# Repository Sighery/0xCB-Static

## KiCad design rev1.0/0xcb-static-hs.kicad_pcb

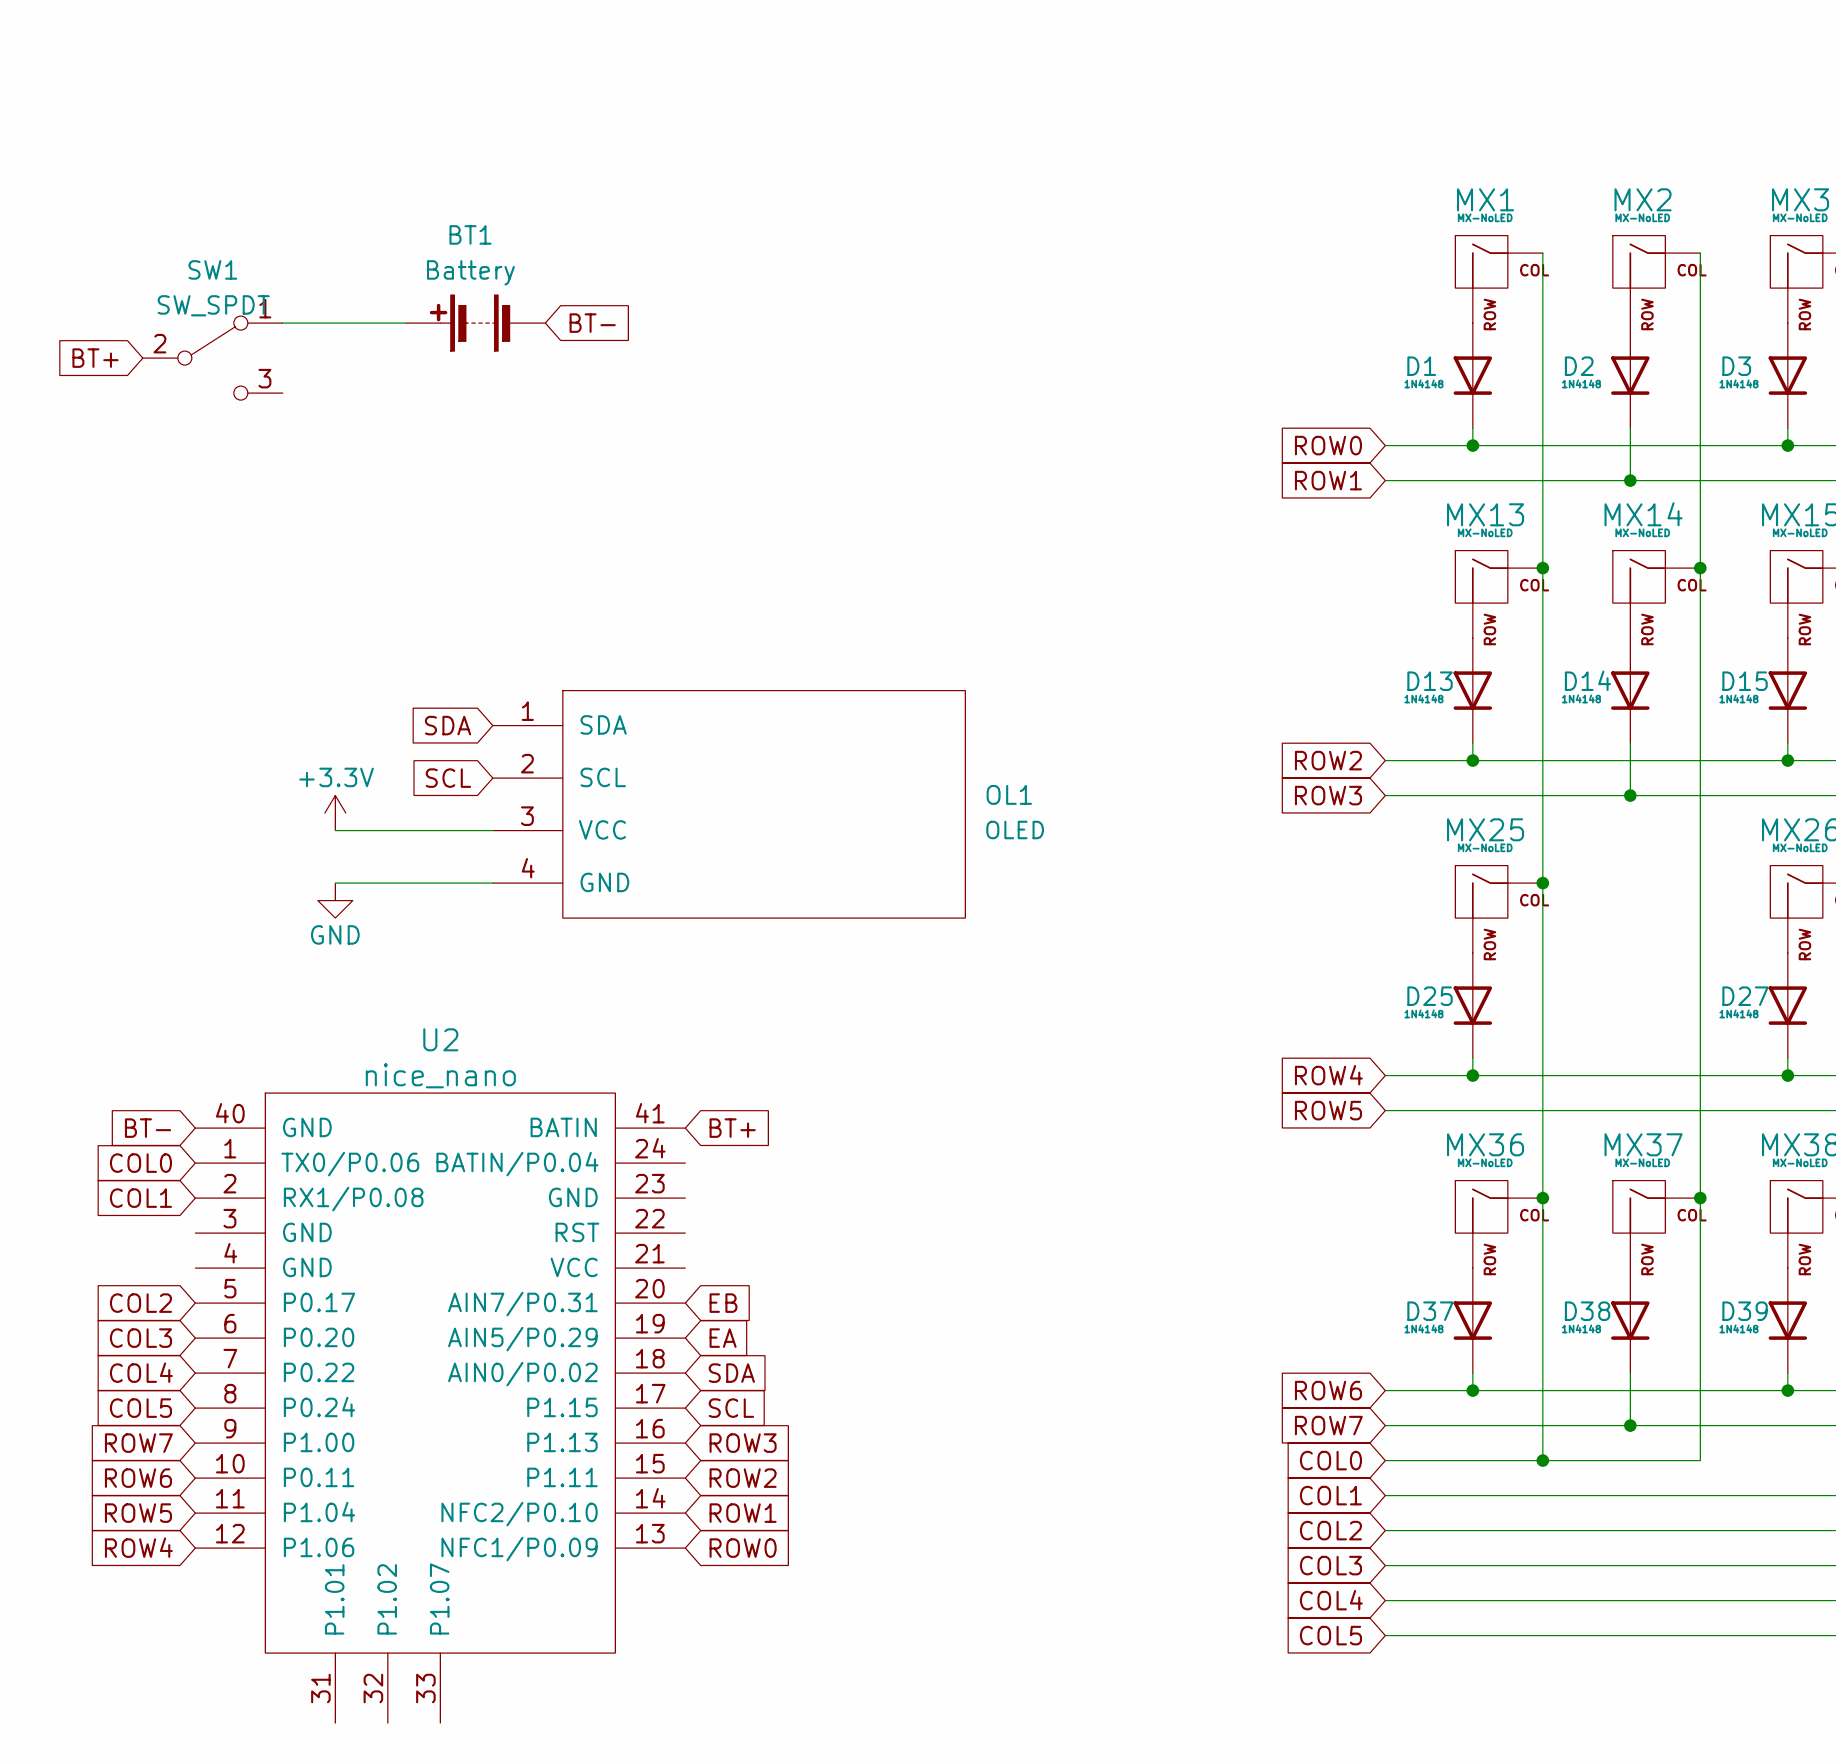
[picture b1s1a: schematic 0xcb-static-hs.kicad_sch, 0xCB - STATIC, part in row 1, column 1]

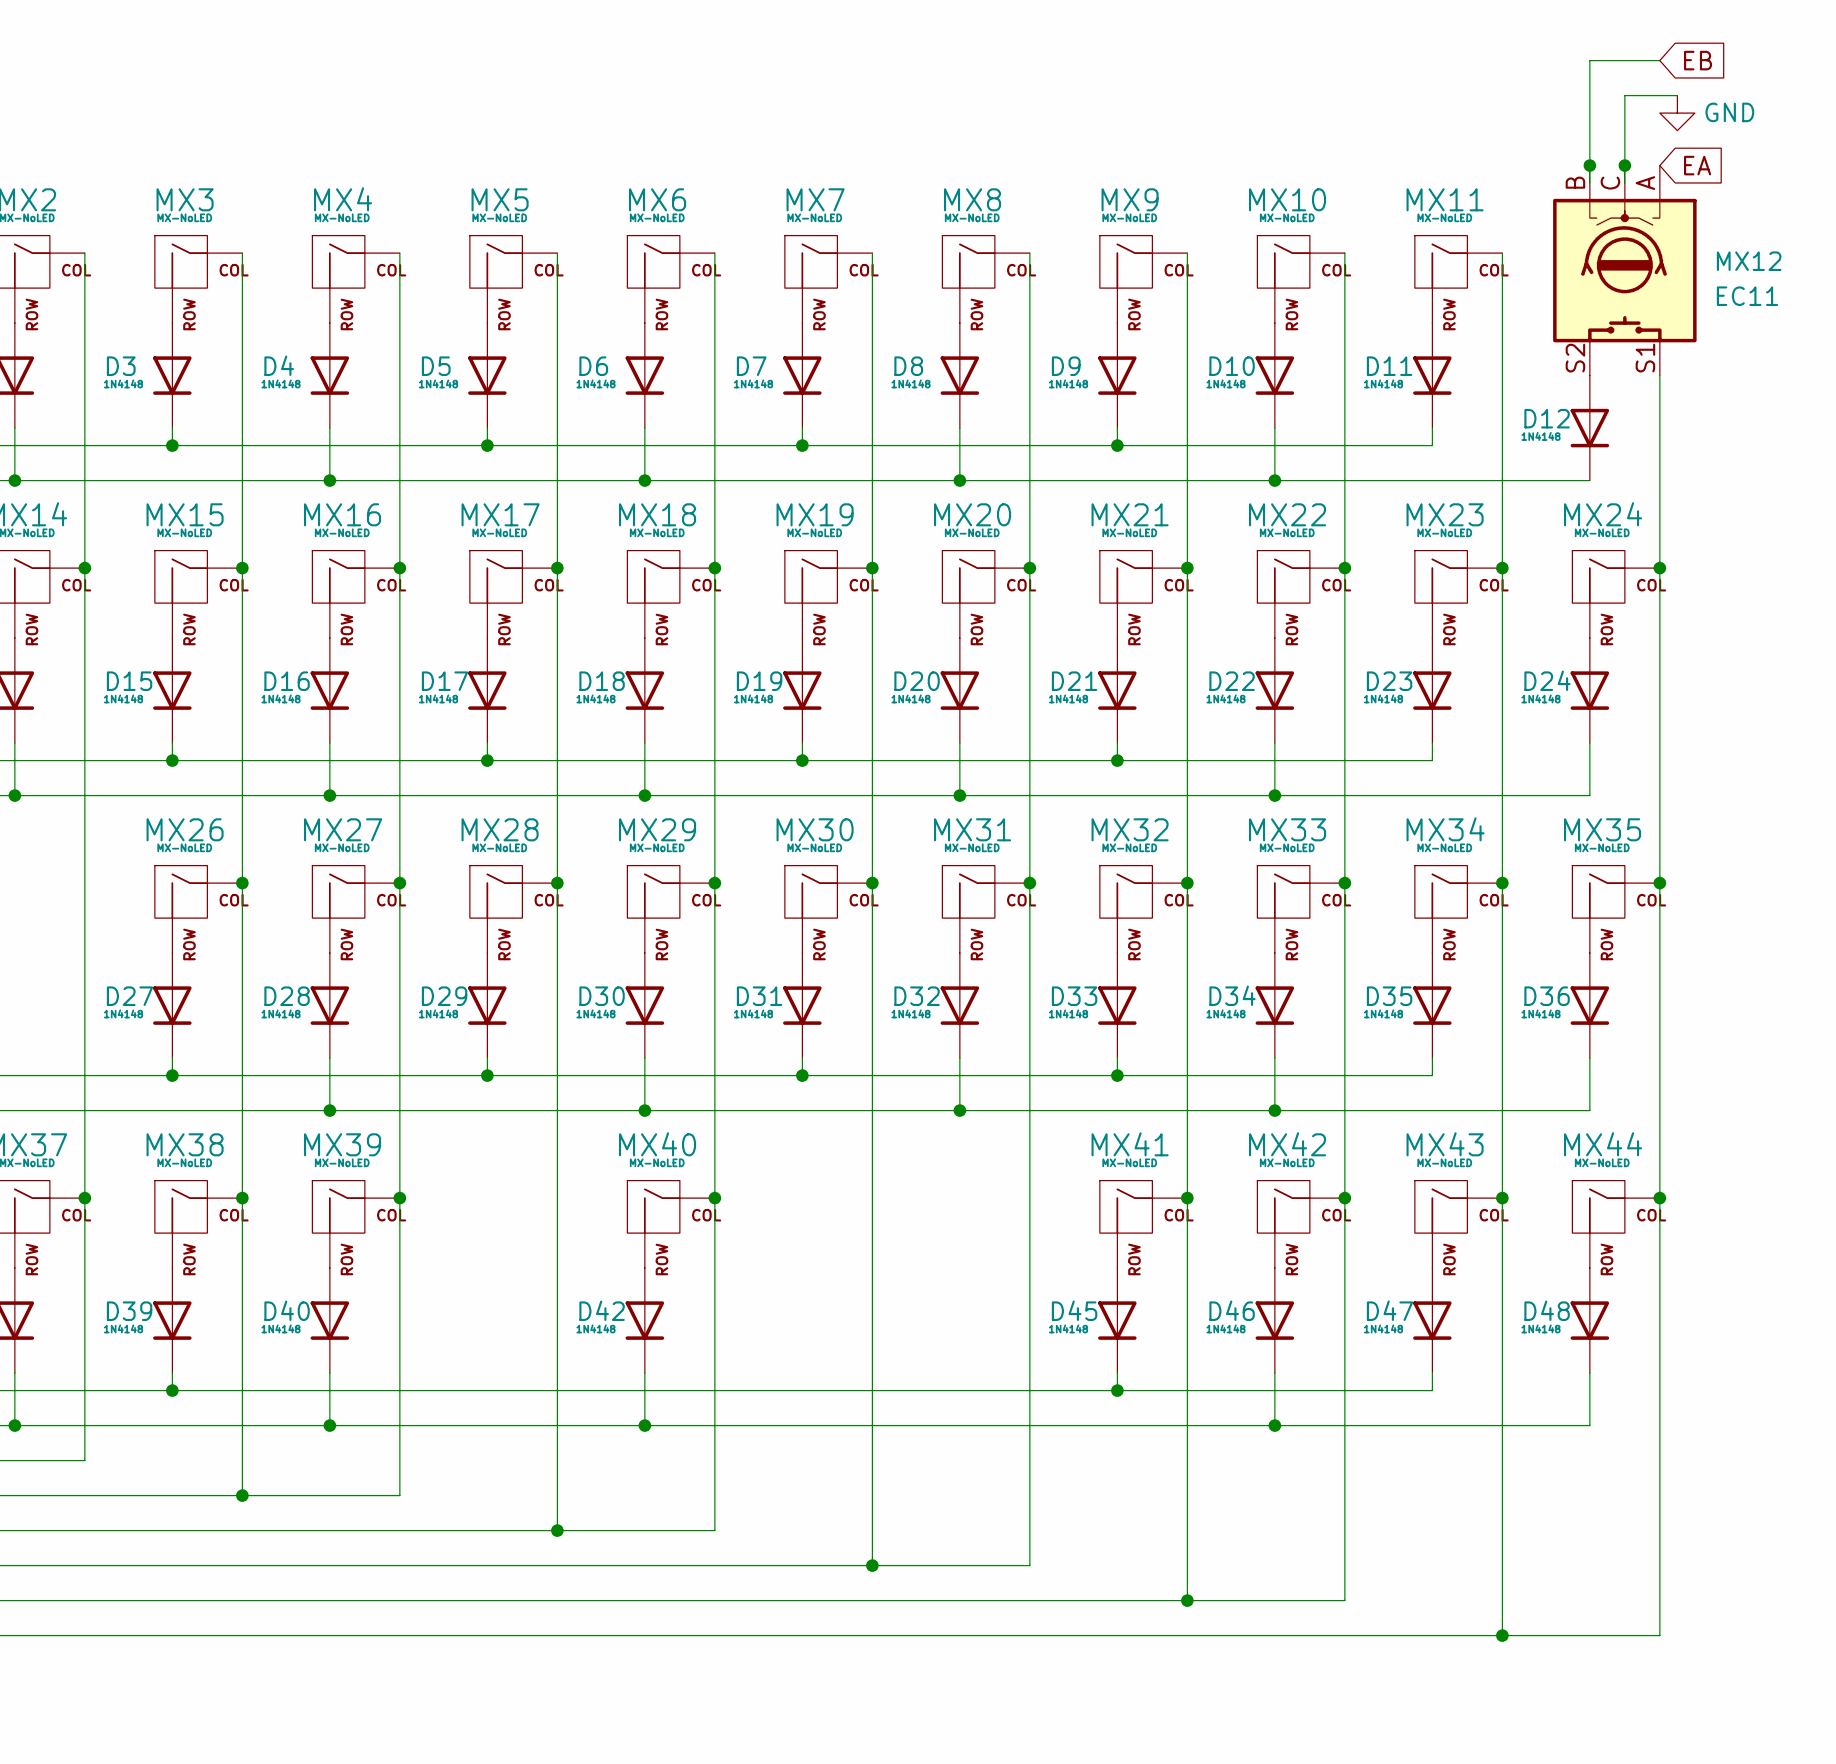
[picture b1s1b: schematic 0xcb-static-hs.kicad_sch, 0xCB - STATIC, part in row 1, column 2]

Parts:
BT1: Battery
D1, D2, D3, D4, D5, D6, D7, D8, D9, D10, D11, D12, D13, D14, D15, D16, D17, D18, D19, D20, D21, D22, D23, D24, D25, D27, D28, D29, D30, D31, D32, D33, D34, D35, D36, D37, D38, D39, D40, D42, D45, D46, D47, D48: 1N4148; D_DO-35_SOD27_P12.70mm_Horizontal; Part Nb. C14538
MX1, MX2, MX3, MX4, MX5, MX6, MX7, MX8, MX9, MX10, MX11, MX14, MX15, MX16, MX17, MX18, MX19, MX20, MX21, MX22, MX24, MX26, MX27, MX28, MX29, MX30, MX31, MX32, MX33, MX34, MX36, MX37, MX38, MX40, MX42, MX43, MX44: MX-NoLED; MXOnly-1U-NoLED; Part Nb. amz
MX12: EC11; RotaryEncoder_Alps_EC11E-Switch_Vertical_H20mm; Part Nb. amz
MX13, MX35: MX-NoLED; MXOnly-1.25U-NoLED; Part Nb. amz
MX23, MX25: MX-NoLED; MXOnly-1.75U-NoLED; Part Nb. amz
MX39: MX-NoLED; MXOnly-2.75U-NoLED; Part Nb. amz
MX41: MX-NoLED; MXOnly-2.25U-NoLED; Part Nb. amz
OL1: OLED; PinSocket_1x04_P2.54mm_Vertical; Part Nb. amz
SW1: SW_SPDT
U2: nice_nano

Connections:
+3.3V: OL1.3 (VCC); also elsewhere on the board
COL0: MX1.1 (COL), MX2.1 (COL), MX13.1 (COL), MX14.1 (COL), MX25.1 (COL), MX36.1 (COL), MX37.1 (COL), U2.1 (TX0/P0.06); also elsewhere on the board
COL1: MX3.1 (COL), MX4.1 (COL), MX15.1 (COL), MX16.1 (COL), MX26.1 (COL), MX27.1 (COL), MX38.1 (COL), MX39.1 (COL), U2.2 (RX1/P0.08); also elsewhere on the board
COL2: MX5.1 (COL), MX6.1 (COL), MX17.1 (COL), MX18.1 (COL), MX28.1 (COL), MX29.1 (COL), MX40.1 (COL), U2.5 (P0.17); also elsewhere on the board
COL3: MX7.1 (COL), MX8.1 (COL), MX19.1 (COL), MX20.1 (COL), MX30.1 (COL), MX31.1 (COL), U2.6 (P0.20); also elsewhere on the board
COL4: MX9.1 (COL), MX10.1 (COL), MX21.1 (COL), MX22.1 (COL), MX32.1 (COL), MX33.1 (COL), MX41.1 (COL), MX42.1 (COL), U2.7 (P0.22); also elsewhere on the board
COL5: MX11.1 (COL), MX12.S1, MX23.1 (COL), MX24.1 (COL), MX34.1 (COL), MX35.1 (COL), MX43.1 (COL), MX44.1 (COL), U2.8 (P0.24); also elsewhere on the board
EA: MX12.A, U2.19 (AIN5/P0.29); also elsewhere on the board
EB: MX12.B, U2.20 (AIN7/P0.31); also elsewhere on the board
GND: MX12.C, OL1.4 (GND); also elsewhere on the board
unnamed: BT1.1 (+), SW1.1 (A)
unnamed: BT1.2 (-), U2.40 (GND)
unnamed: D1.2 (A), MX1.2 (ROW)
unnamed: D2.2 (A), MX2.2 (ROW)
unnamed: D3.2 (A), MX3.2 (ROW)
unnamed: D4.2 (A), MX4.2 (ROW)
unnamed: D5.2 (A), MX5.2 (ROW)
unnamed: D6.2 (A), MX6.2 (ROW)
unnamed: D7.2 (A), MX7.2 (ROW)
unnamed: D8.2 (A), MX8.2 (ROW)
unnamed: D9.2 (A), MX9.2 (ROW)
unnamed: D10.2 (A), MX10.2 (ROW)
unnamed: D11.2 (A), MX11.2 (ROW)
unnamed: D12.2 (A), MX12.S2
unnamed: D13.2 (A), MX13.2 (ROW)
unnamed: D14.2 (A), MX14.2 (ROW)
unnamed: D15.2 (A), MX15.2 (ROW)
unnamed: D16.2 (A), MX16.2 (ROW)
unnamed: D17.2 (A), MX17.2 (ROW)
unnamed: D18.2 (A), MX18.2 (ROW)
unnamed: D19.2 (A), MX19.2 (ROW)
unnamed: D20.2 (A), MX20.2 (ROW)
unnamed: D21.2 (A), MX21.2 (ROW)
unnamed: D22.2 (A), MX22.2 (ROW)
unnamed: D23.2 (A), MX23.2 (ROW)
unnamed: D24.2 (A), MX24.2 (ROW)
unnamed: D25.2 (A), MX25.2 (ROW)
unnamed: D27.2 (A), MX26.2 (ROW)
unnamed: D28.2 (A), MX27.2 (ROW)
unnamed: D29.2 (A), MX28.2 (ROW)
unnamed: D30.2 (A), MX29.2 (ROW)
unnamed: D31.2 (A), MX30.2 (ROW)
unnamed: D32.2 (A), MX31.2 (ROW)
unnamed: D33.2 (A), MX32.2 (ROW)
unnamed: D34.2 (A), MX33.2 (ROW)
unnamed: D35.2 (A), MX34.2 (ROW)
unnamed: D36.2 (A), MX35.2 (ROW)
unnamed: D37.2 (A), MX36.2 (ROW)
unnamed: D38.2 (A), MX37.2 (ROW)
unnamed: D39.2 (A), MX38.2 (ROW)
unnamed: D40.2 (A), MX39.2 (ROW)
unnamed 53: D42.2 (A), MX40.2 (ROW); also elsewhere on the board
unnamed: D45.2 (A), MX41.2 (ROW)
unnamed: D46.2 (A), MX42.2 (ROW)
unnamed: D47.2 (A), MX43.2 (ROW)
unnamed: D48.2 (A), MX44.2 (ROW)
unnamed: SW1.2 (B), U2.41 (BATIN)
ROW0: D1.1 (K), D3.1 (K), D5.1 (K), D7.1 (K), D9.1 (K), D11.1 (K), U2.13 (NFC1/P0.09); also elsewhere on the board
ROW1: D2.1 (K), D4.1 (K), D6.1 (K), D8.1 (K), D10.1 (K), D12.1 (K), U2.14 (NFC2/P0.10); also elsewhere on the board
ROW2: D13.1 (K), D15.1 (K), D17.1 (K), D19.1 (K), D21.1 (K), D23.1 (K), U2.15 (P1.11); also elsewhere on the board
ROW3: D14.1 (K), D16.1 (K), D18.1 (K), D20.1 (K), D22.1 (K), D24.1 (K), U2.16 (P1.13); also elsewhere on the board
ROW4: D25.1 (K), D27.1 (K), D29.1 (K), D31.1 (K), D33.1 (K), D35.1 (K), U2.12 (P1.06); also elsewhere on the board
ROW5: D28.1 (K), D30.1 (K), D32.1 (K), D34.1 (K), D36.1 (K), U2.11 (P1.04); also elsewhere on the board
ROW6: D37.1 (K), D39.1 (K), D45.1 (K), D47.1 (K), U2.10 (P0.11); also elsewhere on the board
ROW7: D38.1 (K), D40.1 (K), D42.1 (K), D46.1 (K), D48.1 (K), U2.9 (P1.00); also elsewhere on the board
SCL: OL1.2 (SCL), U2.17 (P1.15); also elsewhere on the board
SDA: OL1.1 (SDA), U2.18 (AIN0/P0.02); also elsewhere on the board

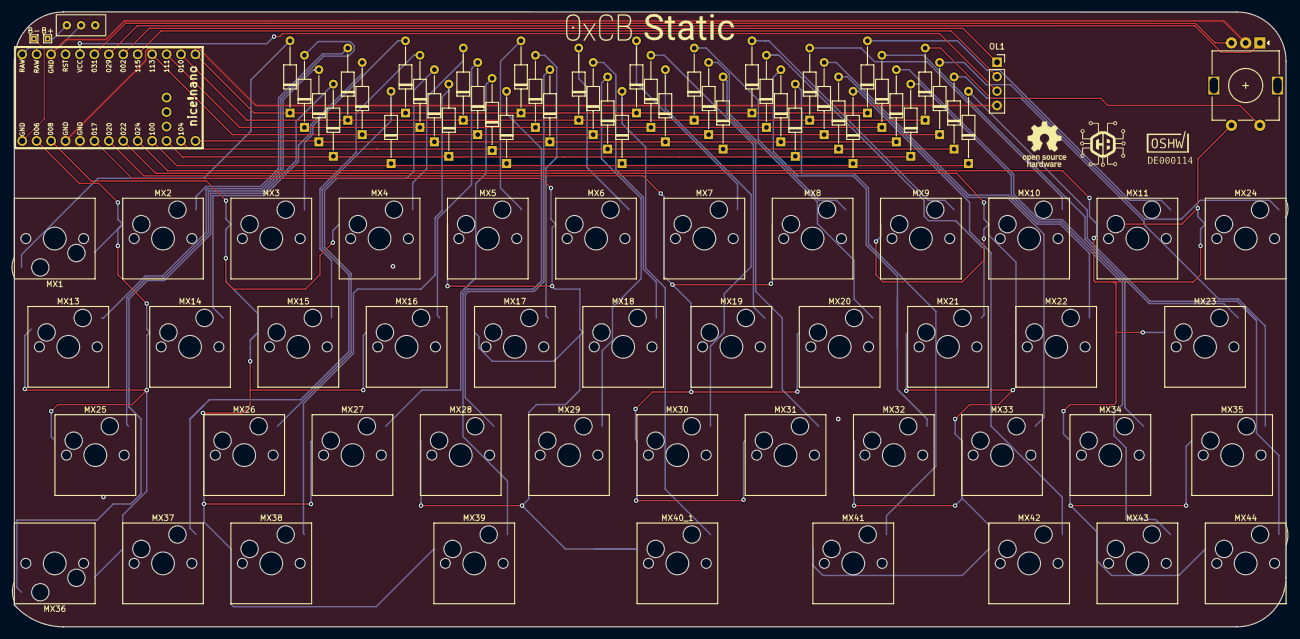
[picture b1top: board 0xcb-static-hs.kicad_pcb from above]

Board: 2 copper layers, 224.5 x 108.2 mm, 97 parts (1 on the bottom side), 66 nets.

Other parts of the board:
B+: TestPoint_THTPad_1.0x1.0mm_Drill0.5mm
B-: TestPoint_THTPad_1.0x1.0mm_Drill0.5mm
L1: font1; svg2mod
L2: font2; svg2mod
L3: OSHW-Logo_7.5x8mm_SilkScreen
L4: LOGO; logo
L5: LOGO; back
MX40_1: MX-NoLED; SW_Hotswap_Kailh_MX_1.00u
U1: nice_nano

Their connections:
+3.3V: U1.21; also elsewhere on the board
BAT+: B+.1, U1.41
BAT-: B-.1, U1.40
COL0: U1.1; also elsewhere on the board
COL1: U1.2; also elsewhere on the board
COL2: MX40_1.1 (COL), U1.5; also elsewhere on the board
COL3: U1.6; also elsewhere on the board
COL4: U1.7; also elsewhere on the board
COL5: U1.8; also elsewhere on the board
EA: U1.19; also elsewhere on the board
EB: U1.20; also elsewhere on the board
GND: U1.3, U1.4, U1.23; also elsewhere on the board
unnamed 53: MX40_1.2 (ROW); also elsewhere on the board
ROW0: U1.13; also elsewhere on the board
ROW1: U1.14; also elsewhere on the board
ROW2: U1.15; also elsewhere on the board
ROW3: U1.16; also elsewhere on the board
ROW4: U1.12; also elsewhere on the board
ROW5: U1.11; also elsewhere on the board
ROW6: U1.10; also elsewhere on the board
ROW7: U1.9; also elsewhere on the board
SCL: U1.17; also elsewhere on the board
SDA: U1.18; also elsewhere on the board

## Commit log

2023-10-29 Add hotswap/nice!nano wireless PCB version
